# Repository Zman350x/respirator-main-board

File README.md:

# Respirator Main Board PCB
## Description

Controls the fans of an active respirator, with added user interface and
various indicators. Made for Intro Engineering Design final project, Fall 2025.

## Pictures

Layout:

3D Render:

Schematic:

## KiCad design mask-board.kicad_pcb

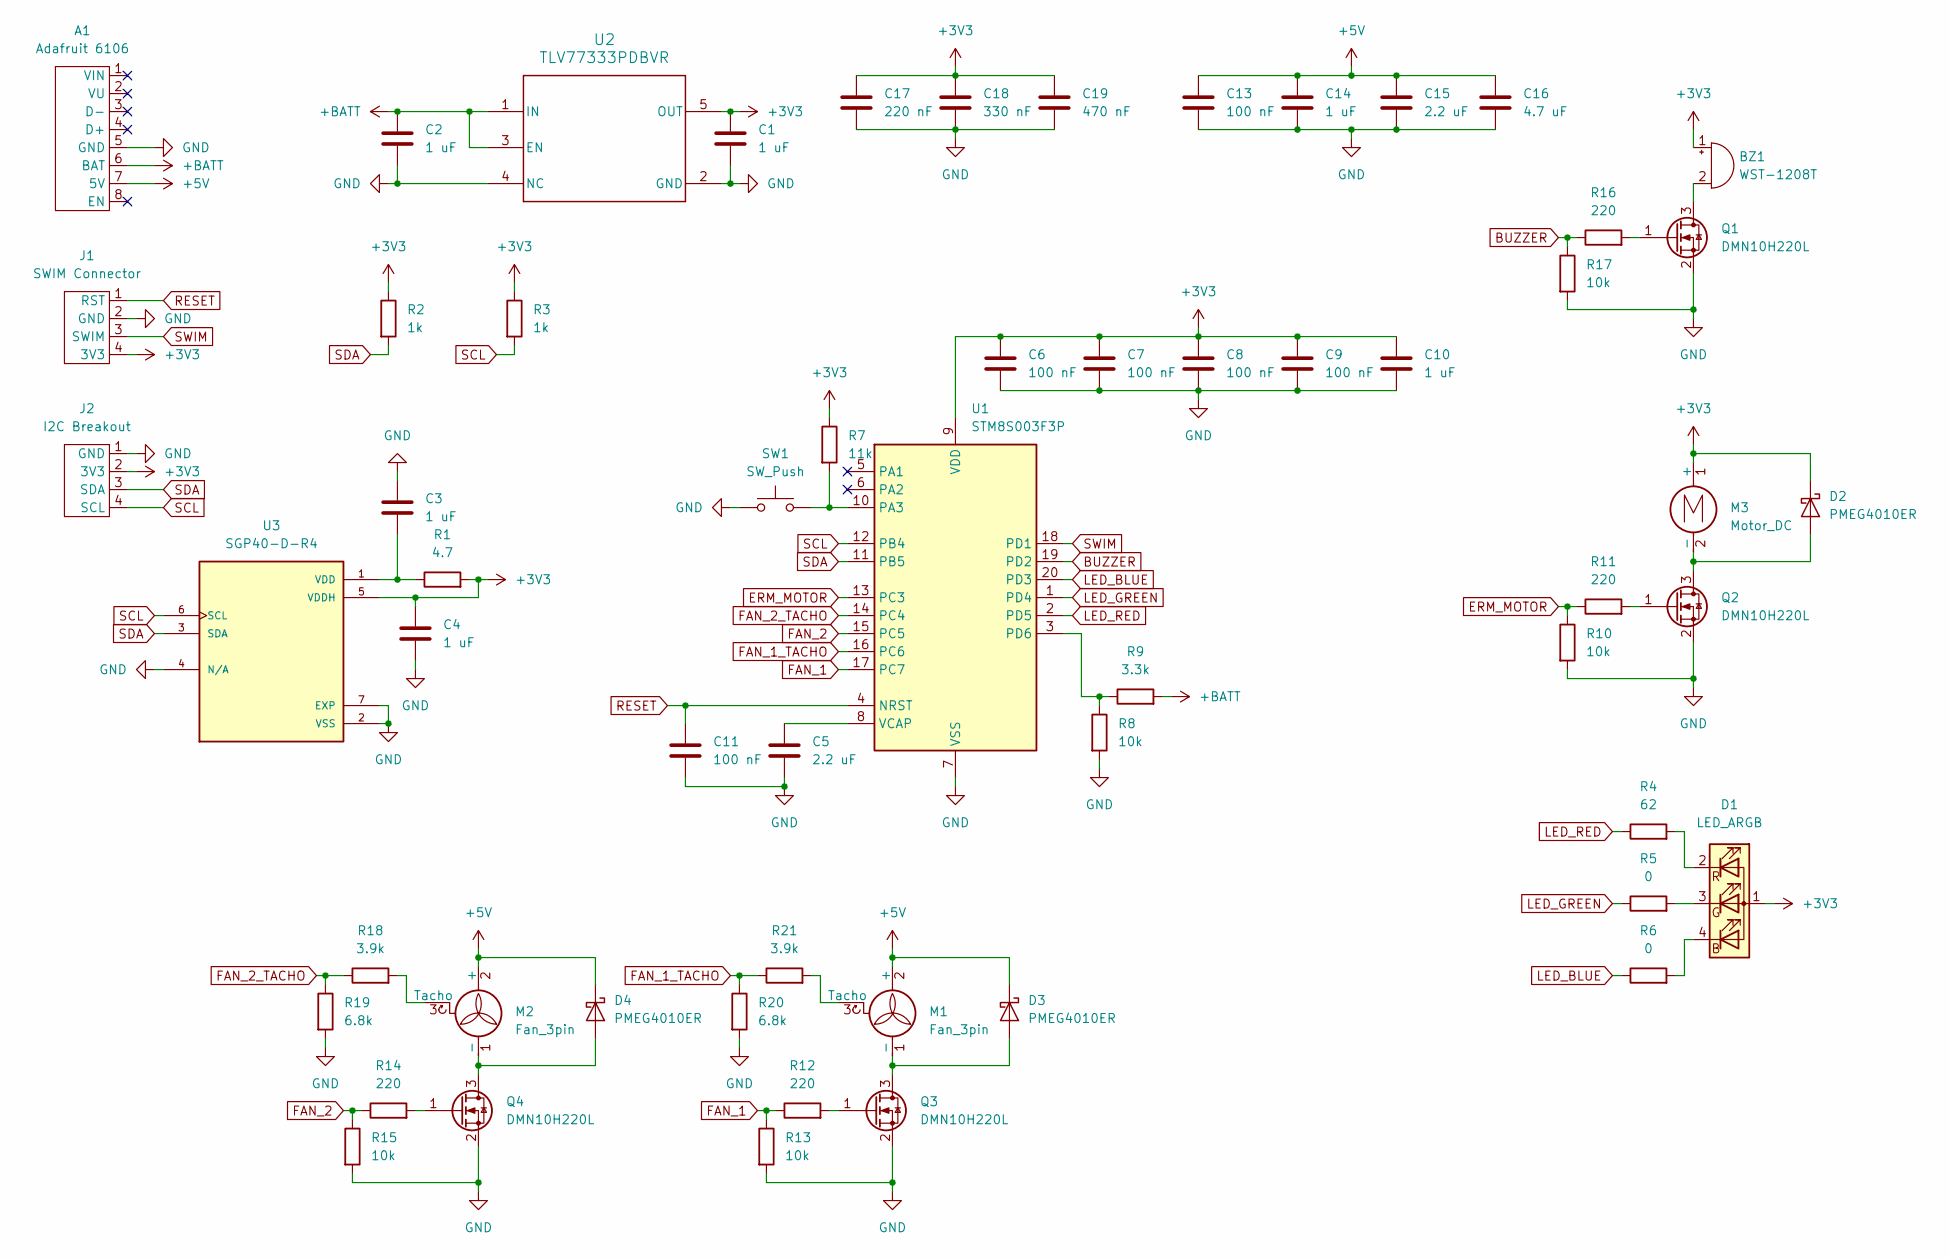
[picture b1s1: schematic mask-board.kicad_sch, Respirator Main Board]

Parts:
A1: Adafruit 6106; PinHeader_1x08_P2.54mm_Vertical
BZ1: WST-1208T; MagneticBuzzer_ProSignal_ABI-009-RC
C1, C2, C3, C4, C10, C14: 1 uF; C_0603_1608Metric
C5, C15: 2.2 uF; C_0603_1608Metric
C6, C7, C8, C9, C11, C13: 100 nF; C_0603_1608Metric
C16: 4.7 uF; C_0603_1608Metric
C17: 220 nF; C_0603_1608Metric
C18: 330 nF; C_0603_1608Metric
C19: 470 nF; C_0603_1608Metric
D1: LED_ARGB; LED_T2133BGR
D2, D3, D4: PMEG4010ER; Nexperia_CFP3_SOD-123W
J1: SWIM Connector; PinSocket_1x04_P2.54mm_Vertical
J2: I2C Breakout; PinSocket_1x04_P2.54mm_Vertical
M1, M2: Fan_3pin; JST-XH-3-pin
M3: Motor_DC; JST-XH-2-pin
Q1, Q2, Q3, Q4: DMN10H220L; SOT-23
R1: 4.7; R_0603_1608Metric
R2, R3: 1k; R_0603_1608Metric
R4: 62; R_0603_1608Metric
R5, R6: 0; R_0603_1608Metric
R7: 11k; R_0603_1608Metric
R8, R10, R13, R15, R17: 10k; R_0603_1608Metric
R9: 3.3k; R_0603_1608Metric
R11, R12, R14, R16: 220; R_0603_1608Metric
R18, R21: 3.9k; R_0603_1608Metric
R19, R20: 6.8k; R_0603_1608Metric
SW1: SW_Push; SW_PUSH_6mm_H5mm
U1: STM8S003F3P; TSSOP-20_4.4x6.5mm_P0.65mm
U2: TLV77333PDBVR; DBV0005A-IPC_A
U3: SGP40-D-R4; XCDR_SGP40-D-R4; PARTREV 1.2

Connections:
+3V3: BZ1.1 (+), C1.1, C4.1, C6.1, C7.1, C8.1, C9.1, C10.1, C17.1, C18.1, C19.1, D1.1 (A), D2.1 (K), J1.4 (3V3), J2.2 (3V3), M3.1 (+), R1.2, R2.1, R3.1, R7.1, U1.9 (VDD), U2.5 (OUT), U3.5 (VDDH)
+5V: A1.7 (5V), C13.1, C14.1, C15.1, C16.1, D3.1 (K), D4.1 (K), M1.2 (+), M2.2 (+)
+BATT: A1.6 (BAT), C2.1, R9.2, U2.1 (IN), U2.3 (EN)
BUZZER: R16.1, R17.1, U1.19 (PD2)
ERM_MOTOR: R10.1, R11.1, U1.13 (PC3)
FAN_1: R12.1, R13.1, U1.17 (PC7)
FAN_1_TACHO: R20.1, R21.1, U1.16 (PC6)
FAN_2: R14.1, R15.1, U1.15 (PC5)
FAN_2_TACHO: R18.1, R19.1, U1.14 (PC4)
GND: A1.5 (GND), C1.2, C2.2, C3.1, C4.2, C5.2, C6.2, C7.2, C8.2, C9.2, C10.2, C11.2, C13.2, C14.2, C15.2, C16.2, C17.2, C18.2, C19.2, J1.2 (GND), J2.1 (GND), Q1.2 (S), Q2.2 (S), Q3.2 (S), Q4.2 (S), R8.2, R10.2, R13.2, R15.2, R17.2, R19.2, R20.2, SW1.1, U1.7 (VSS), U2.2 (GND), U2.4 (NC), U3.2 (VSS), U3.4 (N/A), U3.7 (EXP)
LED_BLUE: R6.1, U1.20 (PD3)
LED_GREEN: R5.1, U1.1 (PD4)
LED_RED: R4.1, U1.2 (PD5)
unnamed: BZ1.2 (-), Q1.3 (D)
unnamed: D1.4 (BK), R6.2
unnamed: D1.3 (GK), R5.2
unnamed: D1.2 (RK), R4.2
unnamed: D2.2 (A), M3.2 (-), Q2.3 (D)
unnamed: D3.2 (A), M1.1 (-), Q3.3 (D)
unnamed: D4.2 (A), M2.1 (-), Q4.3 (D)
unnamed: M1.3 (Tacho), R21.2
unnamed: M2.3 (Tacho), R18.2
unnamed: Q1.1 (G), R16.2
unnamed: Q2.1 (G), R11.2
unnamed: Q3.1 (G), R12.2
unnamed: Q4.1 (G), R14.2
unnamed: R7.2, SW1.2, U1.10 (PA3)
unnamed: R8.1, R9.1, U1.3 (PD6)
unnamed: C5.1, U1.8 (VCAP)
unnamed: C3.2, R1.1, U3.1 (VDD)
RESET: C11.1, J1.1 (RST), U1.4 (NRST)
SCL: J2.4 (SCL), R3.2, U1.12 (PB4), U3.6 (SCL)
SDA: J2.3 (SDA), R2.2, U1.11 (PB5), U3.3 (SDA)
SWIM: J1.3 (SWIM), U1.18 (PD1)

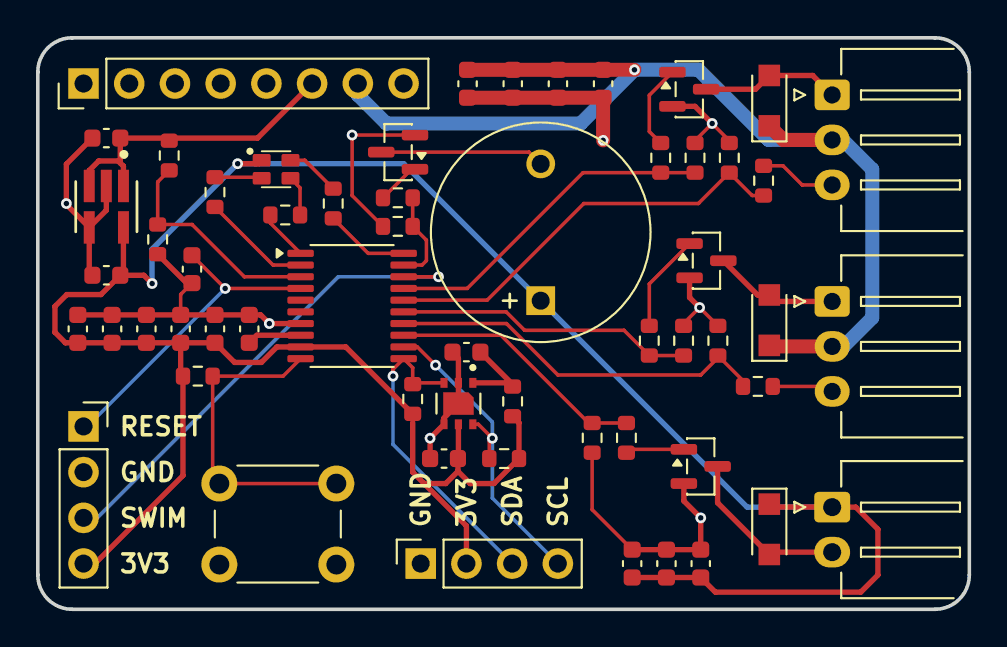
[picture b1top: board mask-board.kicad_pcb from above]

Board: 2 copper layers, 51.8 x 31.8 mm, 59 parts (1 on the bottom side), 34 nets.

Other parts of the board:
Ref**: Val**; logo

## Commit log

2025-11-12 Initial commit: PCB version 1
2025-11-12 Add README and images; Add gitignore
2025-11-12 Update to board V2
2025-11-12 Add LED 3D model
2025-11-12 Update to V3
2025-11-13 Update to V4; Add quarter for scale in 3D model
2025-11-13 Fix trace width and cleanup redundant traces
2025-11-13 Generate gerbers
2025-11-13 Add 3D model of complete PCB with attached battery controller
